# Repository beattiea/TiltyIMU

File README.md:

TiltyIMU
========

This repository contains all files relevant to the TiltyIMU family of circuit boards

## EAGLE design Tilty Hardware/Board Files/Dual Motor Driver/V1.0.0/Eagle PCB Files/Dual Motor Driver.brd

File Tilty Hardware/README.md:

Tilty Hardware
==============

Tilty board Eagle files, libraries, and part datasheets

Hardware revision naming scheme: Production Version . Major revision version . Minor revision version

Examples:  
V0.1.2 = Non-production, first major revision, second minor revision (would become V1.0.0 when it begins production)  
V1.0.0 = First production version, no major or minor revisions  
V1.1.0 = First majorly revised production version with no minor revisions (would become V2.0.0 when it begins production)

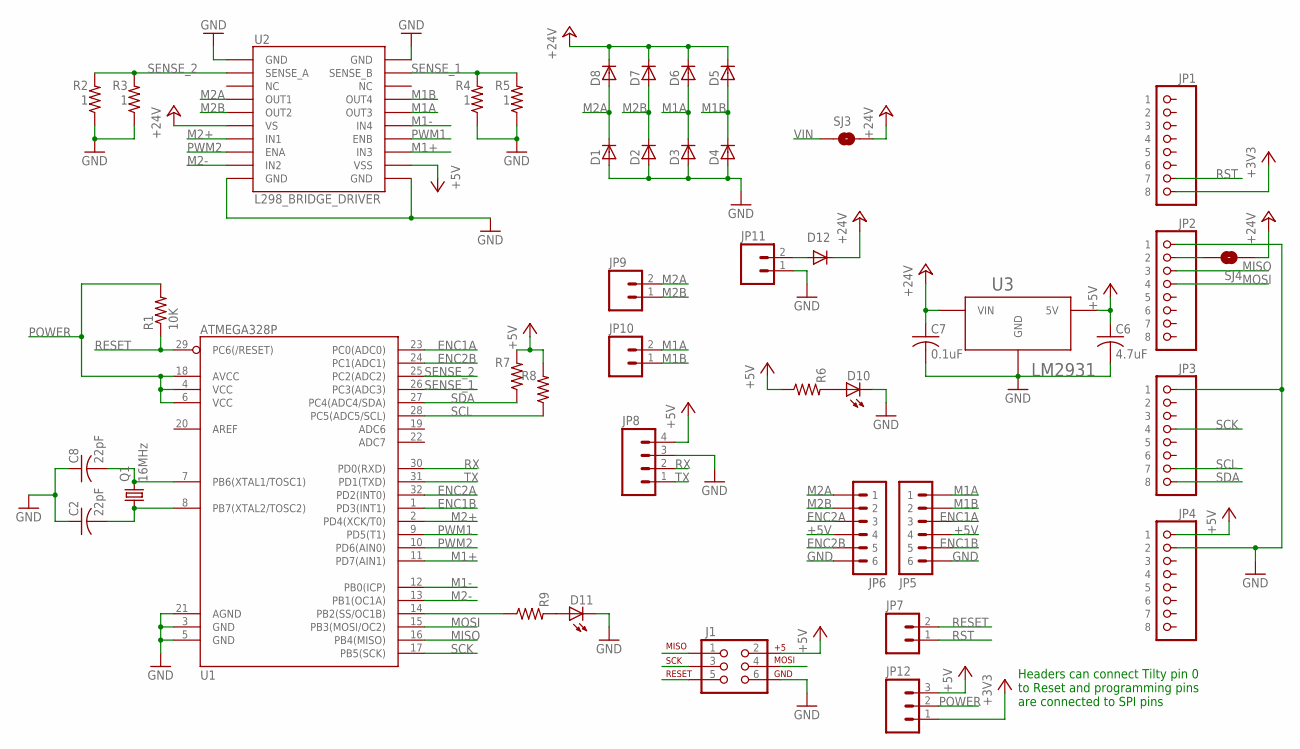
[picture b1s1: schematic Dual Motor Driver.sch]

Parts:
C2, C8: 22pF; C0603
C6: 4.7uF; C0603
C7: 0.1uF; C0603
D1, D2, D3, D4, D5, D6, D7, D8: D-SOD123; SOD123; PART# CDBW140-G
D10, D11: LED-GREENLED-0805_NO_SILK; LED-0805
D12: DIODESMB; SMB-DIODE
J1: AVR_SPI_PRG_62X3_LOCK; 2X3_LOCK
JP1, JP2, JP3, JP4: 8-PIN_HEADER; 8-PIN_RECEPTACLE_LOCK_NO-SS
JP5, JP6: 6PIN-SH_RIGHT_ANGLE; 6PIN-SH_SERIES_RA; PART# SM06B-SRSS-TB(LF)(SN)
JP7, JP9, JP10, JP11: M02PTH; 1X02
JP8: M04PTH; 1X04
JP12: M03PTH; 1X03
Q1: 16MHz; CTS406; PART# 406C35D16M00000
R1: 10K; R0603
R2, R3, R4, R5: 1; R0603
R6, R7, R8, R9: R-US_R0603; R0603
SJ3: SOLDERJUMPERNC; SJ_2S
SJ4: SOLDERJUMPERTRACE; SJ_2S-TRACE
U1: ATMEGA328P; TQFP32-08
U2: L298_BRIDGE_DRIVER; POWERSO20
U3: LM2931; TO263

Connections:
+3V3: JP1.P$8 (8), JP12.1
+5V: C6.1, J1.2, JP4.P$1 (1), JP5.P$4 (4), JP6.P$4 (4), JP8.4, JP12.3, R6.1, R7.2, R8.2, U2.12 (VSS), U3.P$3 (5V)
+24V: C7.1, D5.1 (C), D6.1 (C), D7.1 (C), D8.1 (C), D12.C, SJ3.2, SJ4.1, U2.6 (VS), U3.P$2 (VIN)
ENC1A: JP5.P$3 (3), U1.23 (PC0(ADC0))
ENC1B: JP5.P$5 (5), U1.1 (PD3(INT1))
ENC2A: JP6.P$3 (3), U1.32 (PD2(INT0))
ENC2B: JP6.P$5 (5), U1.24 (PC1(ADC1))
GND: C2.1, C6.2, C7.2, C8.1, D1.2 (A), D2.2 (A), D3.2 (A), D4.2 (A), D10.2 (C), D11.2 (C), J1.6, JP2.P$1 (1), JP3.P$1 (1), JP4.P$2 (2), JP5.P$6 (6), JP6.P$6 (6), JP8.3, JP11.1, R2.1, R3.1, R4.1, R5.1, U1.3 (GND), U1.5 (GND), U1.21 (AGND), U2.1 (GND), U2.10 (GND), U2.11 (GND), U2.20 (GND), U3.P$1 (GND)
M1+: U1.11 (PD7(AIN1)), U2.13 (IN3)
M1-: U1.12 (PB0(ICP)), U2.15 (IN4)
M1A: D3.1 (C), D6.2 (A), JP5.P$1 (1), JP10.2, U2.16 (OUT3)
M1B: D4.1 (C), D5.2 (A), JP5.P$2 (2), JP10.1, U2.17 (OUT4)
M2+: U1.2 (PD4(XCK/T0)), U2.7 (IN1)
M2-: U1.13 (PB1(OC1A)), U2.9 (IN2)
M2A: D1.1 (C), D8.2 (A), JP6.P$1 (1), JP9.2, U2.4 (OUT1)
M2B: D2.1 (C), D7.2 (A), JP6.P$2 (2), JP9.1, U2.5 (OUT2)
MISO: J1.1, JP2.P$3 (3), U1.16 (PB4(MISO))
MOSI: J1.4, JP2.P$4 (4), U1.15 (PB3(MOSI/OC2))
unnamed: D10.1 (A), R6.2
unnamed: D11.1 (A), R9.2
unnamed: R9.1, U1.14 (PB2(SS/OC1B))
unnamed: JP2.P$2 (2), SJ4.2
unnamed: C8.2, Q1.3 (2), U1.7 (PB6(XTAL1/TOSC1))
unnamed: C2.2, Q1.1, U1.8 (PB7(XTAL2/TOSC2))
POWER: JP12.2, R1.2, U1.4 (VCC), U1.6 (VCC), U1.18 (AVCC)
PWM1: U1.9 (PD5(T1)), U2.14 (ENB)
PWM2: U1.10 (PD6(AIN0)), U2.8 (ENA)
RESET: J1.5, JP7.2, R1.1, U1.29 (PC6(/RESET))
RST: JP1.P$7 (7), JP7.1
RX: JP8.2, U1.30 (PD0(RXD))
SCK: J1.3, JP3.P$4 (4), U1.17 (PB5(SCK))
SCL: JP3.P$7 (7), R8.1, U1.28 (PC5(ADC5/SCL))
SDA: JP3.P$8 (8), R7.1, U1.27 (PC4(ADC4/SDA))
SENSE_1: R4.2, R5.2, U1.26 (PC3(ADC3)), U2.19 (SENSE_B)
SENSE_2: R2.2, R3.2, U1.25 (PC2(ADC2)), U2.2 (SENSE_A)
TX: JP8.1, U1.31 (PD1(TXD))
VIN: D12.A, JP11.2, SJ3.1

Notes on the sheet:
Headers can connect Tilty pin 0 to Reset and programming pins are connected to SPI pins

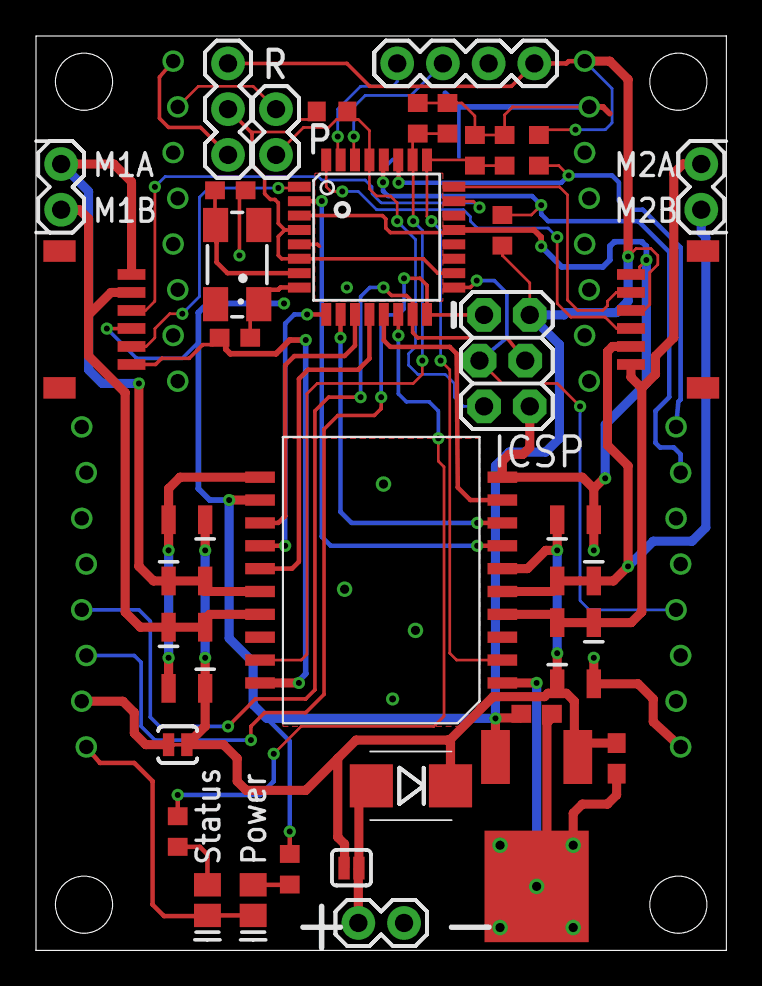
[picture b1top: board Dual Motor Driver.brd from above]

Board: 2 copper layers, 38.4 x 50.8 mm, 43 parts (0 on the bottom side), 37 nets.

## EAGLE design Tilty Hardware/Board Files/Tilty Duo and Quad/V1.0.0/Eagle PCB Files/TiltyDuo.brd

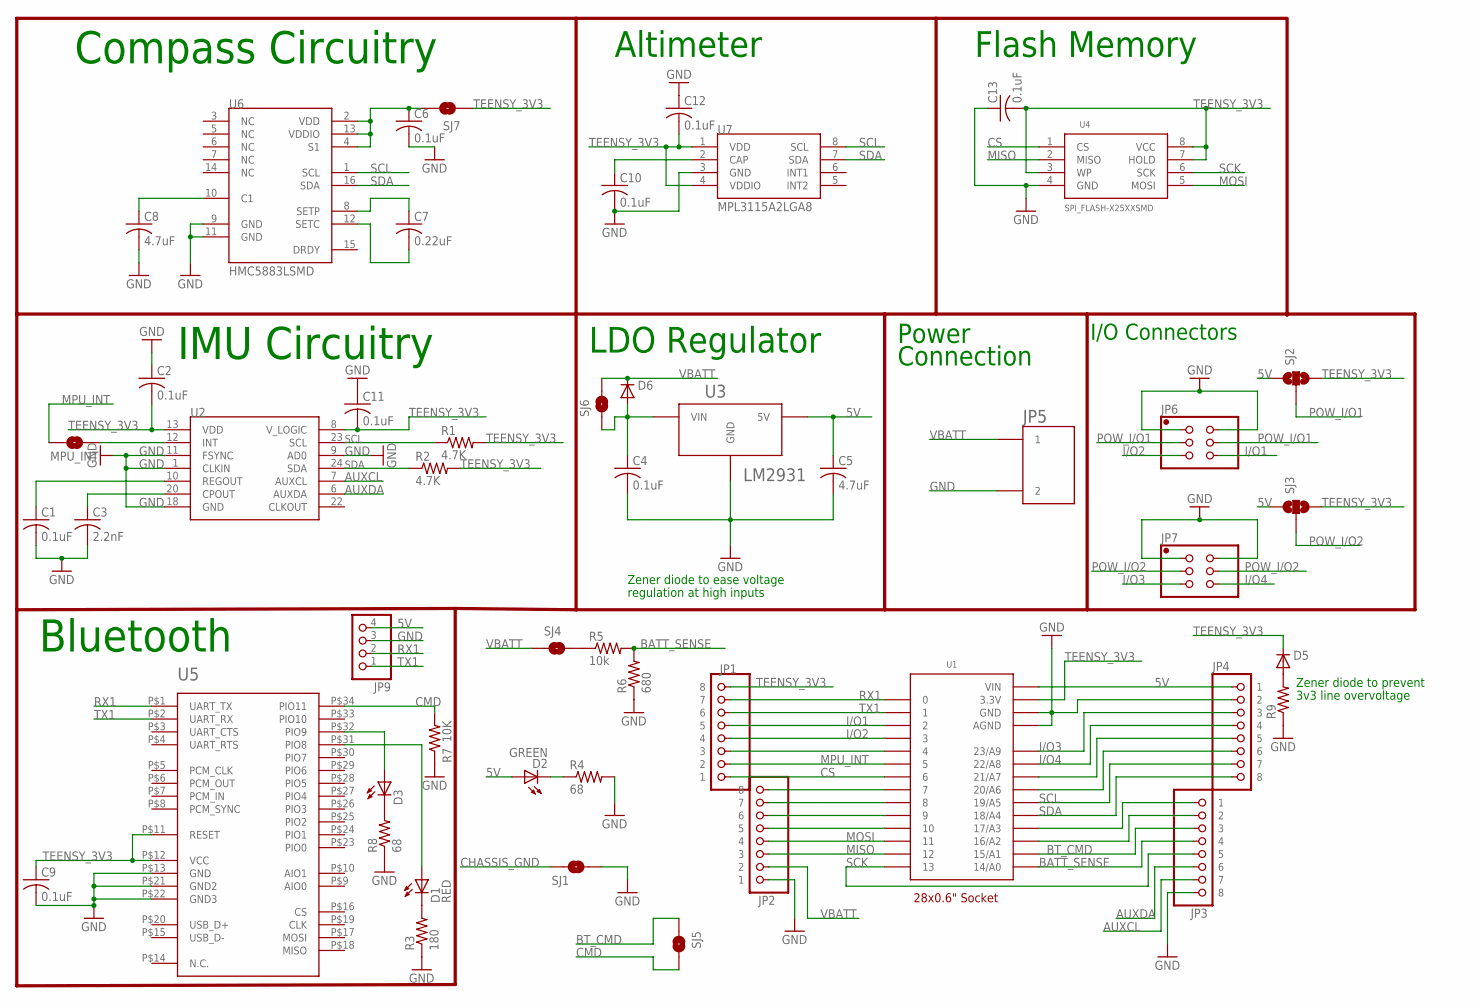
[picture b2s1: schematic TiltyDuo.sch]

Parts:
C1, C2, C4, C6, C9, C10, C11, C12, C13: 0.1uF; C0603
C3: 2.2nF; C0603
C5, C8: 4.7uF; C0603
C7: 0.22uF; C0603
D1: RED; LED-0805
D2: GREEN; LED-0805
D3: YELLOW; LED-0805
D5: DIODESOT23; SOT23-3; PART# BZX84C3V3LT1GOSCT-ND
D6: DIODE-DO214AA; DO214AA
JP1, JP2, JP3, JP4: 8-PIN_HEADER; 8-PIN_RECEPTACLE_LOCK_NO-SS
JP5: 2-POS_SMD_TERM_BLOCK; 2-POS_SMD_TERMINAL_BLOCK; PART# 277-2337-1-ND
JP6, JP7: PINHD-2X32X03_NO_SS_LOCK; 2X03_NO_SS_LOCK
JP9: PINHD-1X41X04_NO_SS_LOCKING; 1X04_NO_SS_LOCKING
MPU_INT: SOLDERJUMPERNO; SJ_2S-NO
R1, R2: 4.7K; R0603
R3: 180; R0603
R4, R8: 68; R0603
R5: 10k; R0603
R6: 680; R0603
R7: 10K; R0603
R9: R-US_R0603; R0603
SJ1: SOLDERJUMPERNO; SJ_2S-NO
SJ2: SOLDERJUMPER_2WAYPASTE1&2; SJ_3_PASTE1&2
SJ3: SOLDERJUMPER_2WAYS; SJ_3
SJ4, SJ5, SJ6, SJ7: SOLDERJUMPERTRACE; SJ_2S-TRACE
U1: TEENSY_3.0_OUTER-PINS28-DIP_SOCKET; 28-DIP; PART# AE10004-ND
U2: MPU-6050; QFN-24
U3: LM2931; TO263
U4: SPI_FLASH-X25XXSMD; SO08; PART# S25FL204K0TMFI043
U5: HC-09_BREAKOUT
U6: HMC5883LSMD; 16LPCC
U7: MPL3115A2LGA8; LGA8

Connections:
5V: C5.1, D2.1 (A), JP4.P$1 (1), JP9.4, SJ2.1, SJ3.1, U1.P$15 (VIN), U3.P$3 (5V)
AUXCL: JP3.P$7 (7), U2.7 (AUXCL)
AUXDA: JP3.P$6 (6), U2.6 (AUXDA)
BATT_SENSE: JP3.P$4 (4), R5.2, R6.2, U1.P$27 (14/A0)
BT_CMD: JP3.P$3 (3), SJ5.1, U1.P$26 (15/A1)
CHASSIS_GND: SJ1.1
CMD: R7.2, SJ5.2, U5.P$34 (PIO11)
CS: JP1.P$1 (1), U1.P$8 (6), U4.1 (CS)
GND: C1.2, C2.1, C3.2, C4.2, C5.2, C6.2, C8.2, C9.2, C10.2, C11.1, C12.1, C13.1, JP2.P$1 (1), JP3.P$8 (8), JP4.P$2 (2), JP5.P$4 (2), JP6.1, JP6.2, JP7.1, JP7.2, JP9.3, R3.1, R4.2, R6.1, R7.1, R8.1, R9.1, SJ1.2, U1.P$1 (GND), U1.P$16 (AGND), U2.1 (CLKIN), U2.9 (AD0), U2.11 (FSYNC), U2.18 (GND), U3.P$1 (GND), U4.4 (GND), U5.P$13 (GND), U5.P$21 (GND2), U5.P$22 (GND3), U6.9 (GND), U6.11 (GND), U7.3 (GND)
I/O1: JP1.P$5 (5), JP6.6, U1.P$4 (2)
I/O2: JP1.P$4 (4), JP6.5, U1.P$5 (3)
I/O3: JP4.P$3 (3), JP7.5, U1.P$18 (23/A9)
I/O4: JP4.P$4 (4), JP7.6, U1.P$19 (22/A8)
MISO: JP2.P$3 (3), U1.P$14 (12), U4.2 (MISO)
MOSI: JP2.P$4 (4), U1.P$13 (11), U4.5 (MOSI)
MPU_INT: JP1.P$2 (2), MPU_INT.1, U1.P$7 (5)
unnamed: C1.1, U2.10 (REGOUT)
unnamed: C3.1, U2.20 (CPOUT)
unnamed: D1.2 (C), R3.2
unnamed: C7.1, U6.8 (SETP)
unnamed: C7.2, U6.12 (SETC)
unnamed: JP1.P$3 (3), U1.P$6 (4)
unnamed: JP2.P$5 (5), U1.P$12 (10)
unnamed: R5.1, SJ4.2
unnamed: JP3.P$1 (1), U1.P$24 (17/A3)
unnamed: C8.1, U6.10 (C1)
unnamed: JP2.P$6 (6), U1.P$11 (9)
unnamed: D2.2 (C), R4.1
unnamed: D1.1 (A), U5.P$31 (PIO8)
unnamed: MPU_INT.2, U2.12 (INT)
unnamed: C6.1, SJ7.2, U6.2 (VDD), U6.4 (S1), U6.13 (VDDIO)
unnamed: JP4.P$5 (5), U1.P$20 (21/A7)
unnamed: JP4.P$6 (6), U1.P$21 (20/A6)
unnamed: C10.1, U7.2 (CAP)
unnamed: D5.1 (A), R9.2
unnamed: JP3.P$2 (2), U1.P$25 (16/A2)
unnamed: D3.2 (C), R8.2
POW_I/O1: JP6.3, JP6.4, SJ2.2
POW_I/O2: JP7.3, JP7.4, SJ3.2
RX1: JP1.P$7 (7), JP9.2, U1.P$2 (0), U5.P$1 (UART_TX)
RX3: JP2.P$8 (8), U1.P$9 (7)
SCK: JP3.P$5 (5), U1.P$28 (13), U4.6 (SCK)
SCL: JP4.P$7 (7), R1.1, U1.P$22 (19/A5), U2.23 (SCL), U6.1 (SCL), U7.8 (SCL)
SDA: JP4.P$8 (8), R2.1, U1.P$23 (18/A4), U2.24 (SDA), U6.16 (SDA), U7.7 (SDA)
TEENSY_3V3: C2.2, C9.1, C11.2, C12.2, C13.2, D5.3 (C), JP1.P$8 (8), R1.2, R2.2, SJ2.3, SJ3.3, SJ7.1, U1.P$17 (3.3V), U2.8 (V_LOGIC), U2.13 (VDD), U4.3 (WP), U4.7 (HOLD), U4.8 (VCC), U5.P$11 (RESET), U5.P$12 (VCC), U7.1 (VDD), U7.4 (VDDIO)
TX1: JP1.P$6 (6), JP9.1, U1.P$3 (1), U5.P$2 (UART_RX)
TX3: JP2.P$7 (7), U1.P$10 (8)
VBATT: C4.1, D6.A, D6.C, JP2.P$2 (2), JP5.P$3 (1), SJ4.1, SJ6.1, SJ6.2, U3.P$2 (VIN)
YEL_LED: D3.1 (A), U5.P$32 (PIO9)

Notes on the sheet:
IMU Circuitry
28x0.6" Socket
LDO Regulator
Bluetooth
Power
Connection
I/O Connectors
Compass Circuitry
Altimeter
Flash Memory
Zener diode to prevent
3v3 line overvoltage
Zener diode to ease voltage
regulation at high inputs

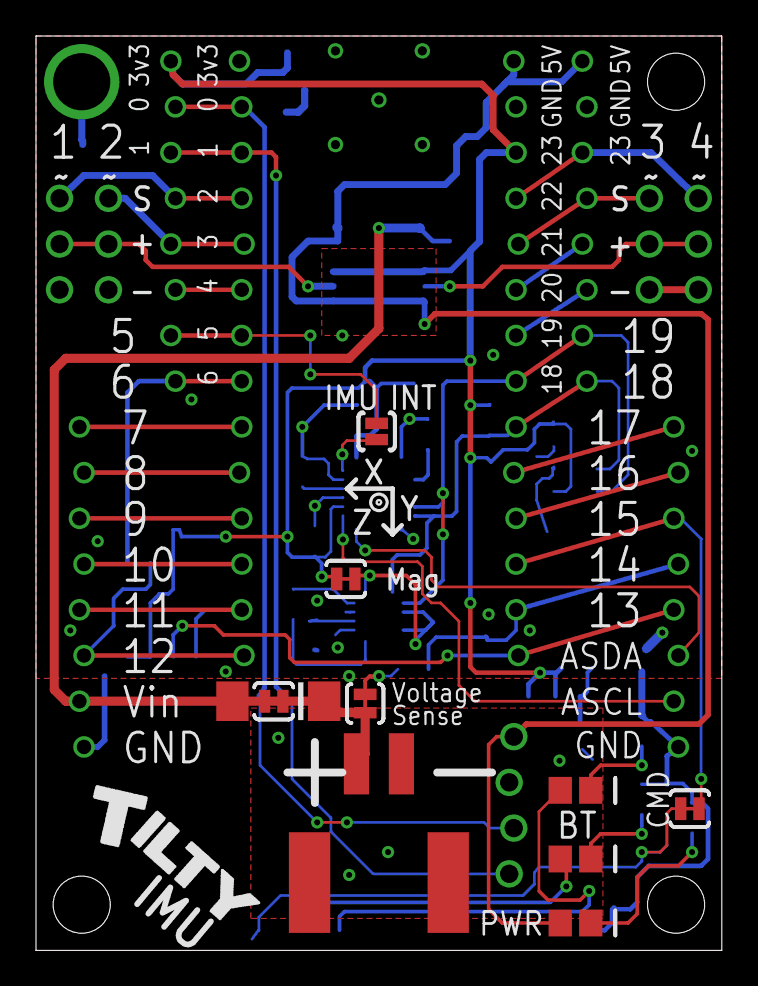
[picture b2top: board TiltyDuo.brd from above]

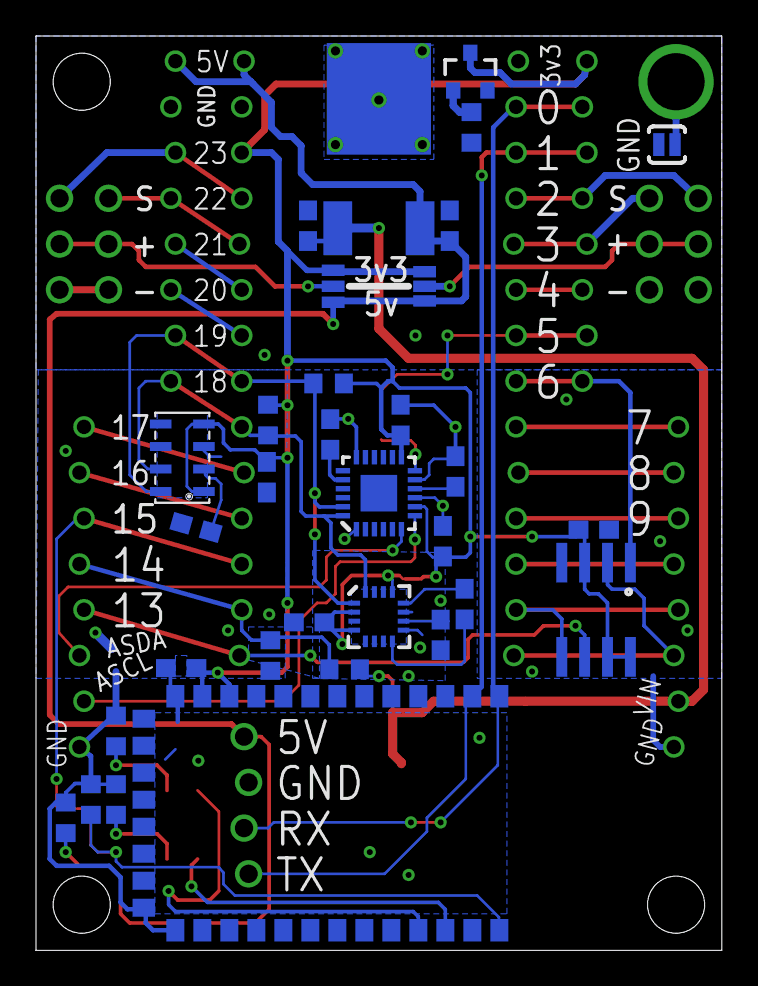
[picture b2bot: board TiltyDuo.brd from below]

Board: 2 copper layers, 38.1 x 50.8 mm, 50 parts (32 on the bottom side), 48 nets.

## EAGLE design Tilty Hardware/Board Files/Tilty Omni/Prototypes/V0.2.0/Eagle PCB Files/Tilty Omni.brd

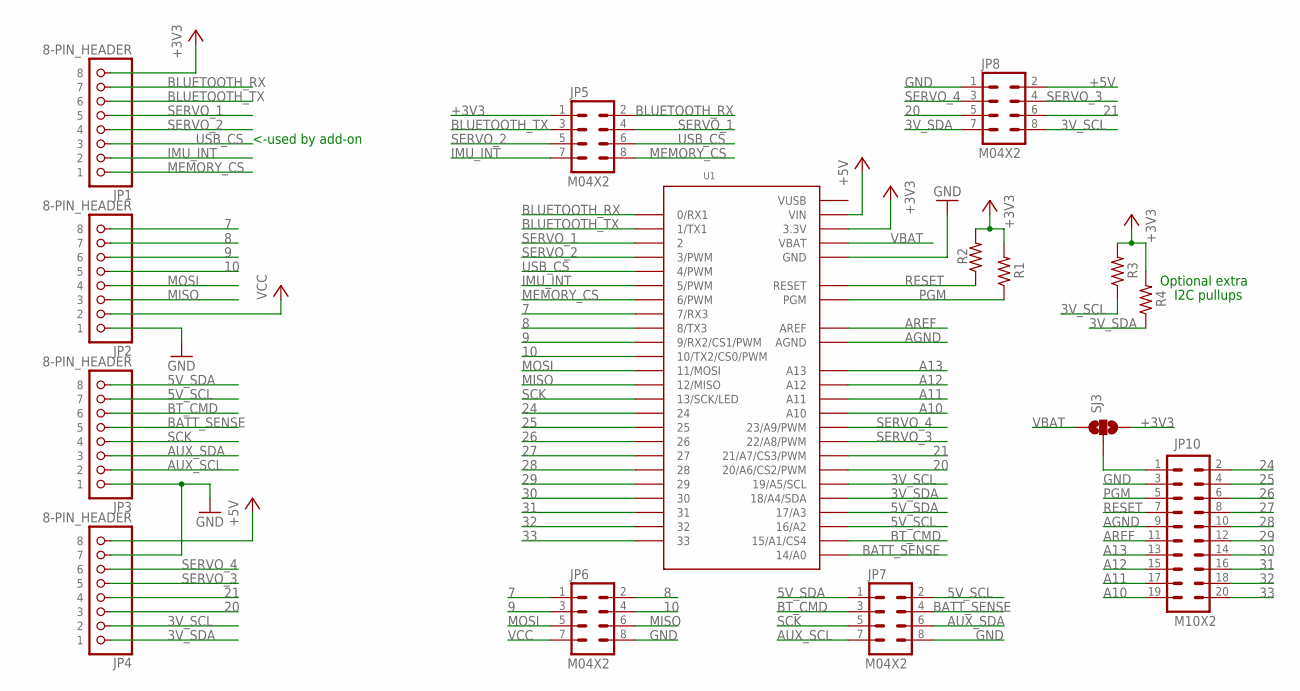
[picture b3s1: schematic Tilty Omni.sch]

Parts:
JP1, JP2, JP3, JP4: 8-PIN_HEADER; 8-PIN_RECEPTACLE_LOCK_NO-SS
JP5, JP6, JP7, JP8: M04X2; 2X4
JP10: M10X2; 2X10
R1, R2, R3, R4: 10k; R0603
SJ3: SOLDERJUMPER_2WAYPASTE2&3; SJ_3_PASTE2&3
U1: TEENSY_3.0_ALLPINS

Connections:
3V_SCL: JP4.P$2 (2), JP8.8, R3.1, U1.19/A5 (19/A5/SCL)
3V_SDA: JP4.P$1 (1), JP8.7, R4.1, U1.18/A4 (18/A4/SDA)
5V_SCL: JP3.P$7 (7), JP7.2, U1.16/A2
5V_SDA: JP3.P$8 (8), JP7.1, U1.17/A3
7: JP2.P$8 (8), JP6.1, U1.7 (7/RX3)
8: JP2.P$7 (7), JP6.2, U1.8 (8/TX3)
9: JP2.P$6 (6), JP6.3, U1.9 (9/RX2/CS1/PWM)
10: JP2.P$5 (5), JP6.4, U1.10 (10/TX2/CS0/PWM)
20: JP4.P$3 (3), JP8.5, U1.20/A6 (20/A6/CS2/PWM)
21: JP4.P$4 (4), JP8.6, U1.21/A7 (21/A7/CS3/PWM)
24: JP10.2, U1.24
25: JP10.4, U1.25
26: JP10.6, U1.26
27: JP10.8, U1.27
28: JP10.10, U1.28
29: JP10.12, U1.29
30: JP10.14, U1.30
31: JP10.16, U1.31
32: JP10.18, U1.32
33: JP10.20, U1.33
+3V3: JP1.P$8 (8), JP5.1, R1.2, R2.2, R3.2, R4.2, SJ3.3, U1.3.3V, U1.3.3V1 (3.3V), U1.3.3V2 (3.3V)
+5V: JP4.P$8 (8), JP8.2, U1.VIN
A10: JP10.19, U1.A10
A11: JP10.17, U1.A11
A12: JP10.15, U1.A12
A13: JP10.13, U1.A13
AGND: JP10.9, U1.AGND
AREF: JP10.11, U1.AREF
AUX_SCL: JP3.P$2 (2), JP7.7
AUX_SDA: JP3.P$3 (3), JP7.6
BATT_SENSE: JP3.P$5 (5), JP7.4, U1.14/A0
BLUETOOTH_RX: JP1.P$7 (7), JP5.2, U1.0 (0/RX1)
BLUETOOTH_TX: JP1.P$6 (6), JP5.3, U1.1 (1/TX1)
BT_CMD: JP3.P$6 (6), JP7.3, U1.15/A1 (15/A1/CS4)
GND: JP2.P$1 (1), JP3.P$1 (1), JP4.P$7 (7), JP6.8, JP7.8, JP8.1, JP10.3, U1.GND, U1.GND1 (GND), U1.GND2 (GND)
IMU_INT: JP1.P$2 (2), JP5.7, U1.5 (5/PWM)
MEMORY_CS: JP1.P$1 (1), JP5.8, U1.6 (6/PWM)
MISO: JP2.P$3 (3), JP6.6, U1.12 (12/MISO)
MOSI: JP2.P$4 (4), JP6.5, U1.11 (11/MOSI)
unnamed: JP10.1, SJ3.2
PGM: JP10.5, R1.1, U1.PGM
RESET: JP10.7, R2.1, U1.RESET
SCK: JP3.P$4 (4), JP7.5, U1.13 (13/SCK/LED)
SERVO_1: JP1.P$5 (5), JP5.4, U1.2
SERVO_2: JP1.P$4 (4), JP5.5, U1.3 (3/PWM)
SERVO_3: JP4.P$5 (5), JP8.4, U1.22/A8 (22/A8/PWM)
SERVO_4: JP4.P$6 (6), JP8.3, U1.23/A9 (23/A9/PWM)
USB_CS: JP1.P$3 (3), JP5.6, U1.4 (4/PWM)
VBAT: SJ3.1, U1.VBAT
VCC: JP2.P$2 (2), JP6.7
VUSB: U1.VUSB

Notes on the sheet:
<-used by add-on
Optional extra
I2C pullups

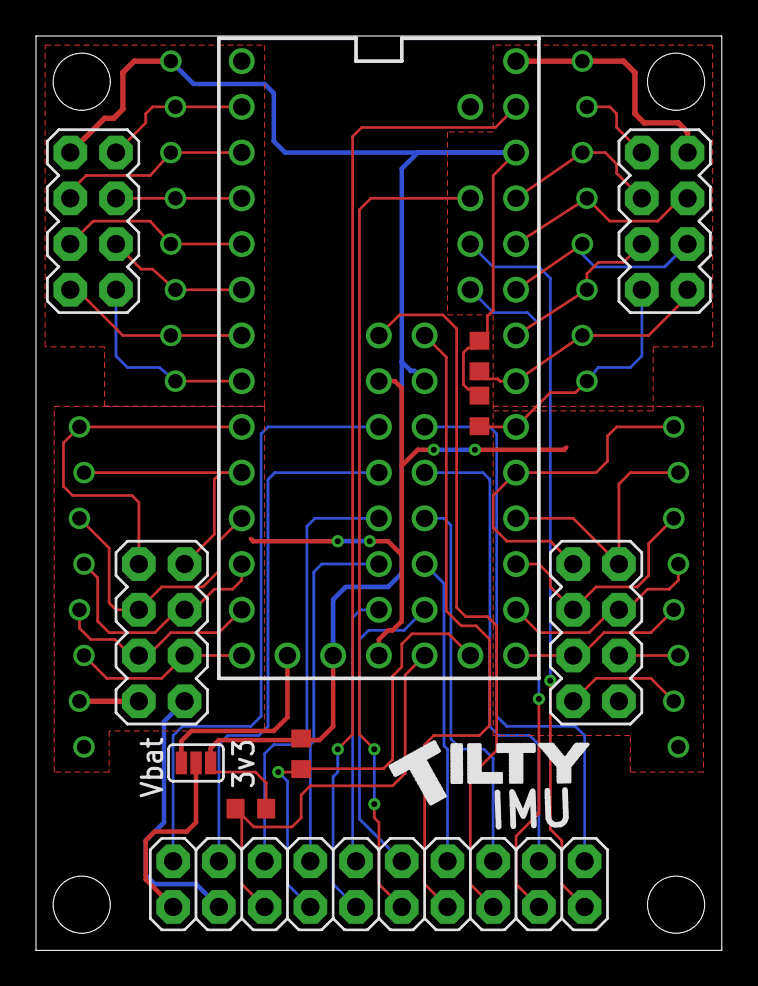
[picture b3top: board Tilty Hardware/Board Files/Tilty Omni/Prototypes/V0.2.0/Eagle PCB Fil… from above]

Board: 2 copper layers, 38.1 x 50.8 mm, 15 parts (0 on the bottom side), 50 nets.

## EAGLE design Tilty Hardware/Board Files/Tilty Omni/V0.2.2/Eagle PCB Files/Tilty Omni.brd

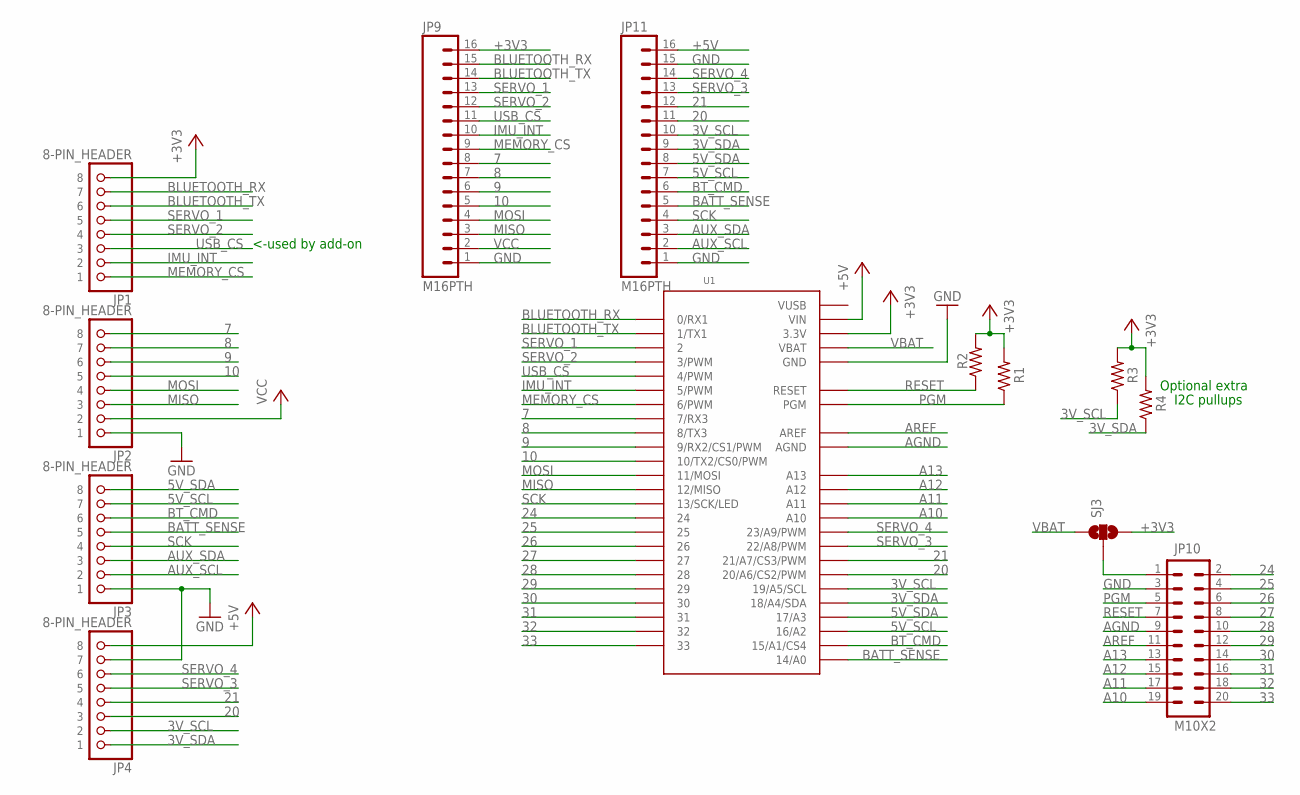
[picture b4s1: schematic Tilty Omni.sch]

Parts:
JP1, JP2, JP3, JP4: 8-PIN_HEADER; 8-PIN_RECEPTACLE_LOCK_NO-SS
JP9, JP11: M16PTH; 1X16
JP10: M10X2; 2X10
R1, R2, R3, R4: 10k; R0603
SJ3: SOLDERJUMPER_2WAYPASTE2&3; SJ_3_PASTE2&3
U1: TEENSY_3.0_ALLPINS

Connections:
3V_SCL: JP4.P$2 (2), JP11.10, R3.1, U1.19/A5 (19/A5/SCL)
3V_SDA: JP4.P$1 (1), JP11.9, R4.1, U1.18/A4 (18/A4/SDA)
5V_SCL: JP3.P$7 (7), JP11.7, U1.16/A2
5V_SDA: JP3.P$8 (8), JP11.8, U1.17/A3
7: JP2.P$8 (8), JP9.8, U1.7 (7/RX3)
8: JP2.P$7 (7), JP9.7, U1.8 (8/TX3)
9: JP2.P$6 (6), JP9.6, U1.9 (9/RX2/CS1/PWM)
10: JP2.P$5 (5), JP9.5, U1.10 (10/TX2/CS0/PWM)
20: JP4.P$3 (3), JP11.11, U1.20/A6 (20/A6/CS2/PWM)
21: JP4.P$4 (4), JP11.12, U1.21/A7 (21/A7/CS3/PWM)
24: JP10.2, U1.24
25: JP10.4, U1.25
26: JP10.6, U1.26
27: JP10.8, U1.27
28: JP10.10, U1.28
29: JP10.12, U1.29
30: JP10.14, U1.30
31: JP10.16, U1.31
32: JP10.18, U1.32
33: JP10.20, U1.33
+3V3: JP1.P$8 (8), JP9.16, R1.2, R2.2, R3.2, R4.2, SJ3.3, U1.3.3V, U1.3.3V1 (3.3V), U1.3.3V2 (3.3V)
+5V: JP4.P$8 (8), JP11.16, U1.VIN
A10: JP10.19, U1.A10
A11: JP10.17, U1.A11
A12: JP10.15, U1.A12
A13: JP10.13, U1.A13
AGND: JP10.9, U1.AGND
AREF: JP10.11, U1.AREF
AUX_SCL: JP3.P$2 (2), JP11.2
AUX_SDA: JP3.P$3 (3), JP11.3
BATT_SENSE: JP3.P$5 (5), JP11.5, U1.14/A0
BLUETOOTH_RX: JP1.P$7 (7), JP9.15, U1.0 (0/RX1)
BLUETOOTH_TX: JP1.P$6 (6), JP9.14, U1.1 (1/TX1)
BT_CMD: JP3.P$6 (6), JP11.6, U1.15/A1 (15/A1/CS4)
GND: JP2.P$1 (1), JP3.P$1 (1), JP4.P$7 (7), JP9.1, JP10.3, JP11.1, JP11.15, U1.GND, U1.GND1 (GND), U1.GND2 (GND)
IMU_INT: JP1.P$2 (2), JP9.10, U1.5 (5/PWM)
MEMORY_CS: JP1.P$1 (1), JP9.9, U1.6 (6/PWM)
MISO: JP2.P$3 (3), JP9.3, U1.12 (12/MISO)
MOSI: JP2.P$4 (4), JP9.4, U1.11 (11/MOSI)
unnamed: JP10.1, SJ3.2
PGM: JP10.5, R1.1, U1.PGM
RESET: JP10.7, R2.1, U1.RESET
SCK: JP3.P$4 (4), JP11.4, U1.13 (13/SCK/LED)
SERVO_1: JP1.P$5 (5), JP9.13, U1.2
SERVO_2: JP1.P$4 (4), JP9.12, U1.3 (3/PWM)
SERVO_3: JP4.P$5 (5), JP11.13, U1.22/A8 (22/A8/PWM)
SERVO_4: JP4.P$6 (6), JP11.14, U1.23/A9 (23/A9/PWM)
USB_CS: JP1.P$3 (3), JP9.11, U1.4 (4/PWM)
VBAT: SJ3.1, U1.VBAT
VCC: JP2.P$2 (2), JP9.2
VUSB: U1.VUSB

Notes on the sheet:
<-used by add-on
Optional extra
I2C pullups

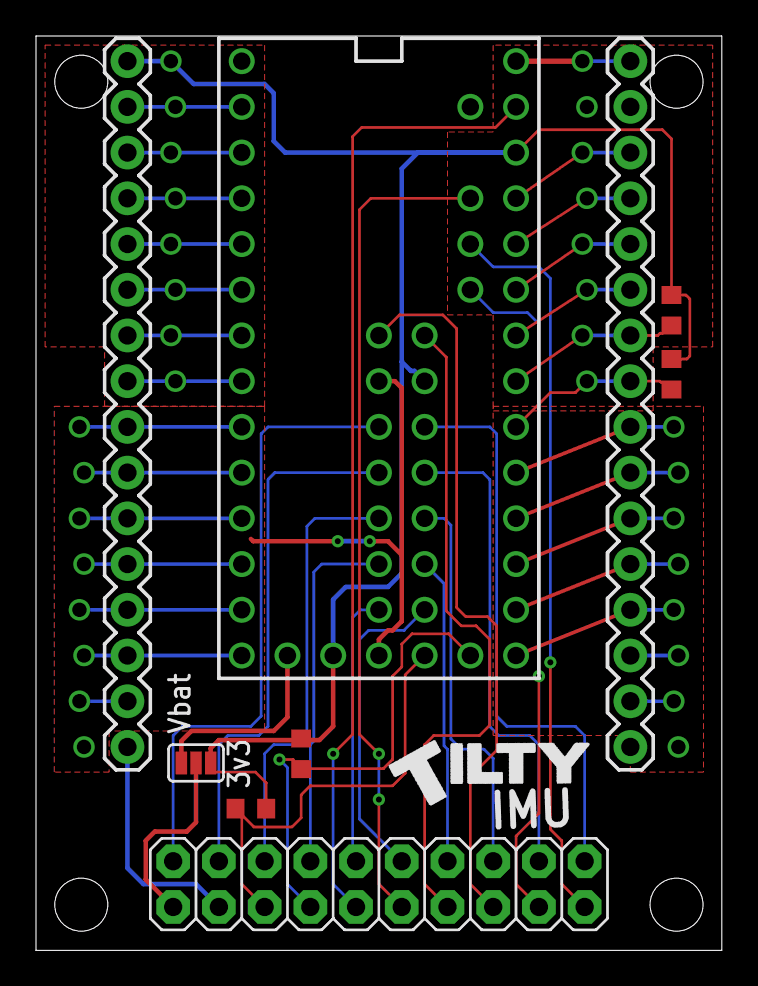
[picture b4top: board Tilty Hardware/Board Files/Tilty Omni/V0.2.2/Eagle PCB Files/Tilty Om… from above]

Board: 2 copper layers, 38.1 x 50.8 mm, 13 parts (0 on the bottom side), 50 nets.

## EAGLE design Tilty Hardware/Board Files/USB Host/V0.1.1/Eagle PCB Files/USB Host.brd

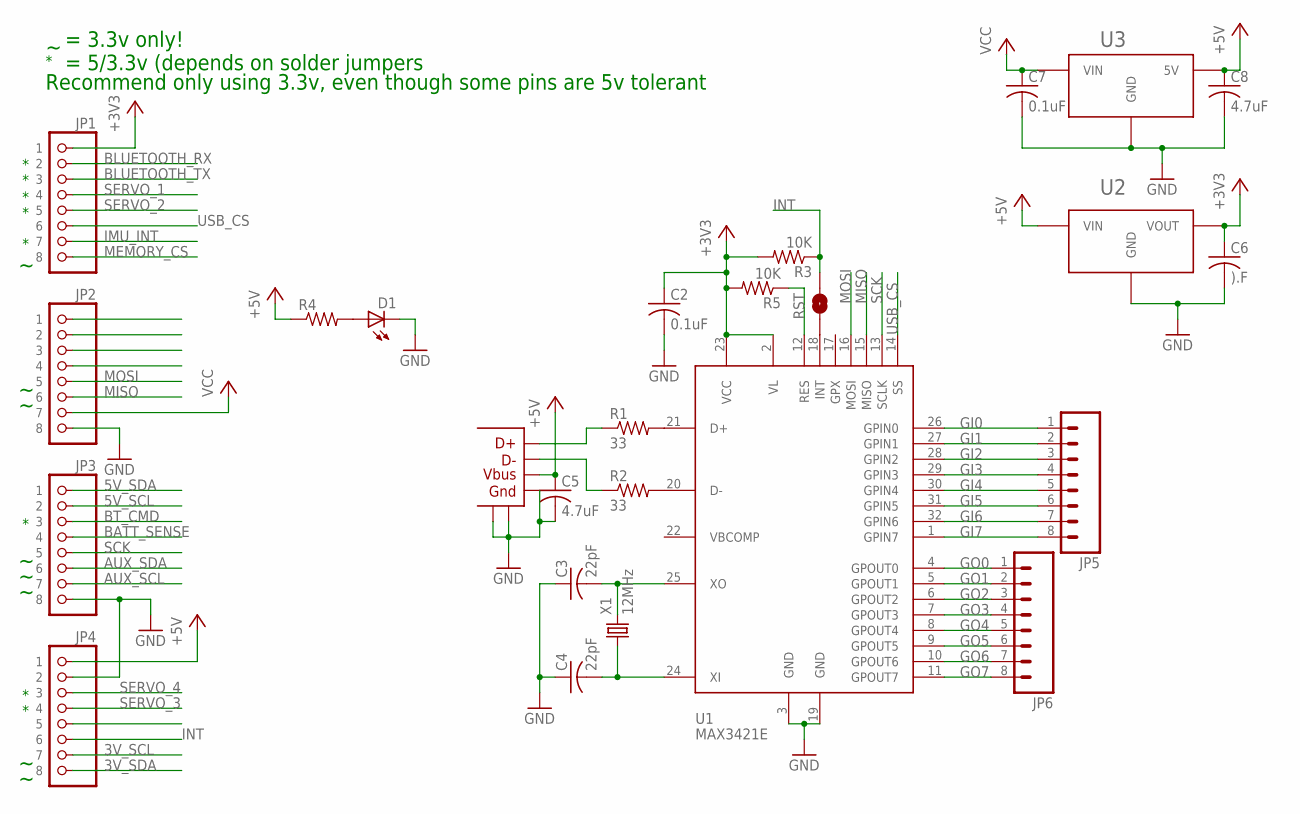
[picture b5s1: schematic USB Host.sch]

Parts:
C2, C7: 0.1uF; C0603
C3, C4: 22pF; C0603
C5, C8: 4.7uF; C0603
C6: ).F; C0603
D1: LED-GREENLED-0805_NO_SILK; LED-0805
JP1, JP2, JP3, JP4: 8-PIN_HEADER; 8-PIN_RECEPTACLE_LOCK_NO-SS
JP5, JP6: M081X08; 1X08
R1, R2: 33; R0603
R3, R5: 10K; R0603
R4: R-US_R0603; R0603
SJ1: SOLDERJUMPERTRACE; SJ_2S-TRACE
U1: MAX3421E; TQFP32_8MIL
U2: AP7313SOT23R; SOT23
U3: LM2931; TO263
U$1: USB_SOCKETTYPE-A; USB_SOCKET; PART# USB-A1HSW6
X1: 12MHz; CRYSTAL-TXC-7A; PART# 7A-12.000MAAE-T

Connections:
3V_SCL: JP4.P$7 (7)
3V_SDA: JP4.P$8 (8)
5V_SCL: JP3.P$2 (2)
5V_SDA: JP3.P$1 (1)
+3V3: C2.1, C6.1, JP1.P$1 (1), R3.2, R5.2, U1.2 (VL), U1.23 (VCC), U2.P$2 (VOUT)
+5V: C5.1, C8.1, JP4.P$1 (1), R4.1, U2.P$3 (VIN), U3.P$3 (5V), U$1.P$1 (VBUS)
AUX_SCL: JP3.P$7 (7)
AUX_SDA: JP3.P$6 (6)
BATT_SENSE: JP3.P$4 (4)
BLUETOOTH_RX: JP1.P$2 (2)
BLUETOOTH_TX: JP1.P$3 (3)
BT_CMD: JP3.P$3 (3)
GI0: JP5.1, U1.26 (GPIN0)
GI1: JP5.2, U1.27 (GPIN1)
GI2: JP5.3, U1.28 (GPIN2)
GI3: JP5.4, U1.29 (GPIN3)
GI4: JP5.5, U1.30 (GPIN4)
GI5: JP5.6, U1.31 (GPIN5)
GI6: JP5.7, U1.32 (GPIN6)
GI7: JP5.8, U1.1 (GPIN7)
GND: C2.2, C3.1, C4.1, C5.2, C6.2, C7.2, C8.2, D1.2 (C), JP2.P$8 (8), JP3.P$8 (8), JP4.P$2 (2), U1.3 (GND), U1.19 (GND), U2.P$1 (GND), U3.P$1 (GND), U$1.P$4 (GND), U$1.P$5, U$1.P$6
GO0: JP6.1, U1.4 (GPOUT0)
GO1: JP6.2, U1.5 (GPOUT1)
GO2: JP6.3, U1.6 (GPOUT2)
GO3: JP6.4, U1.7 (GPOUT3)
GO4: JP6.5, U1.8 (GPOUT4)
GO5: JP6.6, U1.9 (GPOUT5)
GO6: JP6.7, U1.10 (GPOUT6)
GO7: JP6.8, U1.11 (GPOUT7)
IMU_INT: JP1.P$7 (7)
INT: JP4.P$6 (6), R3.1, SJ1.2
MEMORY_CS: JP1.P$8 (8)
MISO: JP2.P$6 (6), U1.15 (MISO)
MOSI: JP2.P$5 (5), U1.16 (MOSI)
unnamed: R2.2, U1.20 (D-)
unnamed: R1.2, U1.21 (D+)
unnamed: R2.1, U$1.P$2 (D-)
unnamed: R1.1, U$1.P$3 (D+)
unnamed: D1.1 (A), R4.2
unnamed: SJ1.1, U1.18 (INT)
unnamed: C4.2, U1.24 (XI), X1.P$1 (1)
unnamed: C3.2, U1.25 (XO), X1.P$2 (2)
RST: R5.1, U1.12 (RES)
SCK: JP3.P$5 (5), U1.13 (SCLK)
SERVO_1: JP1.P$4 (4)
SERVO_2: JP1.P$5 (5)
SERVO_3: JP4.P$4 (4)
SERVO_4: JP4.P$3 (3)
USB_CS: JP1.P$6 (6), U1.14 (SS)
VCC: C7.1, JP2.P$7 (7), U3.P$2 (VIN)

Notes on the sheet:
= 3.3v only!
= 5/3.3v (depends on solder jumpers
Recommend only using 3.3v, even though some pins are 5v tolerant

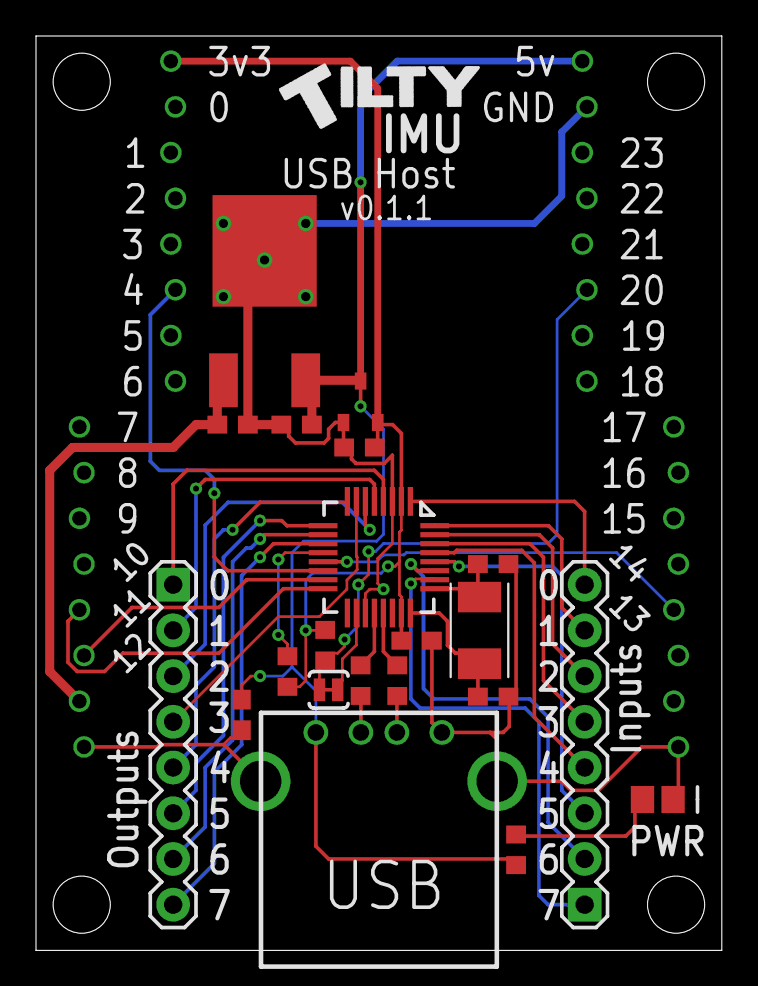
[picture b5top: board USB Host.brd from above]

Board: 2 copper layers, 38.1 x 50.8 mm, 25 parts (0 on the bottom side), 34 nets.

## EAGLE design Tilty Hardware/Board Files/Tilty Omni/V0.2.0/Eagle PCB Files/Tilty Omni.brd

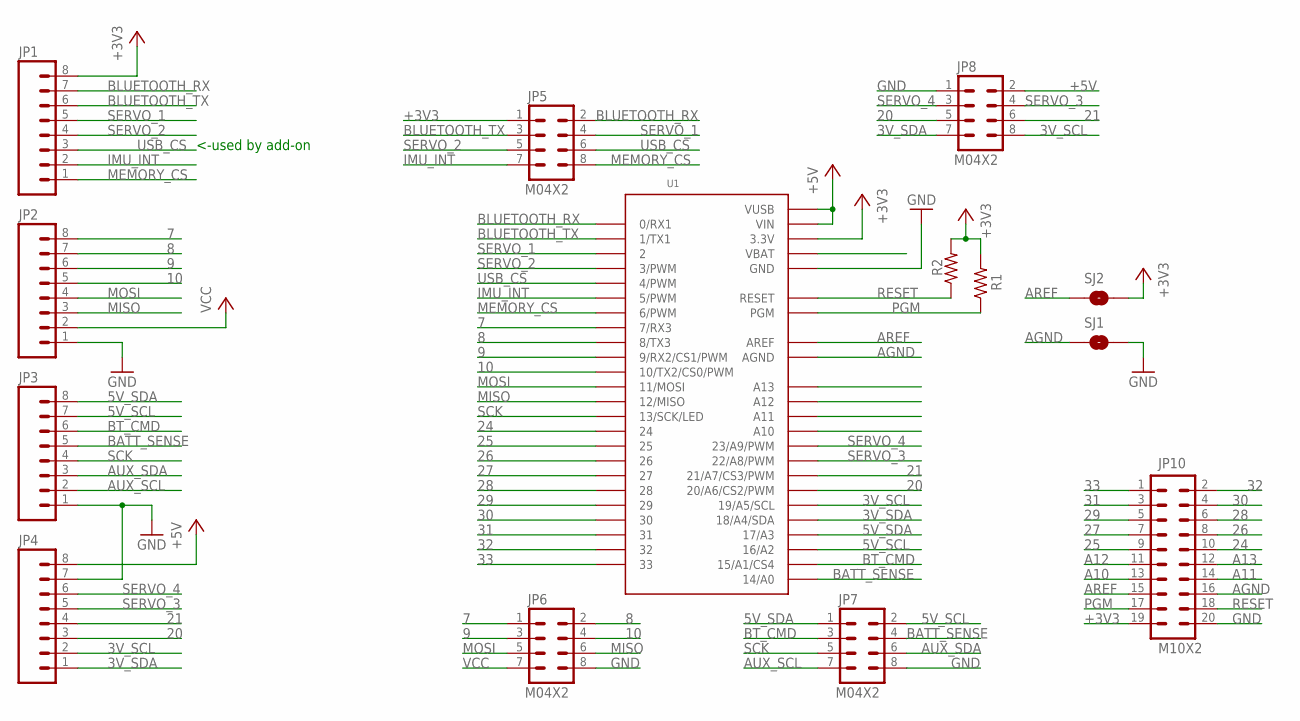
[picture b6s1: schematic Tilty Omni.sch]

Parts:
JP1, JP2, JP3, JP4: M081X08; 1X08
JP5, JP6, JP7, JP8: M04X2; 2X4
JP10: M10X2; 2X10
R1, R2: 10k; R0603
SJ1, SJ2: SOLDERJUMPERTRACE; SJ_2S-TRACE
U1: TEENSY_3.0_ALLPINS

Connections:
3V_SCL: JP4.2, JP8.8, U1.19/A5 (19/A5/SCL)
3V_SDA: JP4.1, JP8.7, U1.18/A4 (18/A4/SDA)
5V_SCL: JP3.7, JP7.2, U1.16/A2
5V_SDA: JP3.8, JP7.1, U1.17/A3
7: JP2.8, JP6.1, U1.7 (7/RX3)
8: JP2.7, JP6.2, U1.8 (8/TX3)
9: JP2.6, JP6.3, U1.9 (9/RX2/CS1/PWM)
10: JP2.5, JP6.4, U1.10 (10/TX2/CS0/PWM)
20: JP4.3, JP8.5, U1.20/A6 (20/A6/CS2/PWM)
21: JP4.4, JP8.6, U1.21/A7 (21/A7/CS3/PWM)
24: JP10.10, U1.24
25: JP10.9, U1.25
26: JP10.8, U1.26
27: JP10.7, U1.27
28: JP10.6, U1.28
29: JP10.5, U1.29
30: JP10.4, U1.30
31: JP10.3, U1.31
32: JP10.2, U1.32
33: JP10.1, U1.33
+3V3: JP1.8, JP5.1, JP10.19, R1.2, R2.2, SJ2.2, U1.3.3V, U1.3.3V1 (3.3V), U1.3.3V2 (3.3V)
+5V: JP4.8, JP8.2, U1.VIN, U1.VUSB
A10: JP10.13
A11: JP10.14
A12: JP10.11
A13: JP10.12, U1.A13
AGND: JP10.16, SJ1.1, U1.AGND
AREF: JP10.15, SJ2.1, U1.AREF
AUX_SCL: JP3.2, JP7.7
AUX_SDA: JP3.3, JP7.6
BATT_SENSE: JP3.5, JP7.4, U1.14/A0
BLUETOOTH_RX: JP1.7, JP5.2, U1.0 (0/RX1)
BLUETOOTH_TX: JP1.6, JP5.3, U1.1 (1/TX1)
BT_CMD: JP3.6, JP7.3, U1.15/A1 (15/A1/CS4)
GND: JP2.1, JP3.1, JP4.7, JP6.8, JP7.8, JP8.1, JP10.20, SJ1.2, U1.GND, U1.GND1 (GND), U1.GND2 (GND)
IMU_INT: JP1.2, JP5.7, U1.5 (5/PWM)
MEMORY_CS: JP1.1, JP5.8, U1.6 (6/PWM)
MISO: JP2.3, JP6.6, U1.12 (12/MISO)
MOSI: JP2.4, JP6.5, U1.11 (11/MOSI)
PGM: JP10.17, R1.1, U1.PGM
RESET: JP10.18, R2.1, U1.RESET
SCK: JP3.4, JP7.5, U1.13 (13/SCK/LED)
SERVO_1: JP1.5, JP5.4, U1.2
SERVO_2: JP1.4, JP5.5, U1.3 (3/PWM)
SERVO_3: JP4.5, JP8.4, U1.22/A8 (22/A8/PWM)
SERVO_4: JP4.6, JP8.3, U1.23/A9 (23/A9/PWM)
USB_CS: JP1.3, JP5.6, U1.4 (4/PWM)
VCC: JP2.2, JP6.7

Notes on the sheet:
<-used by add-on

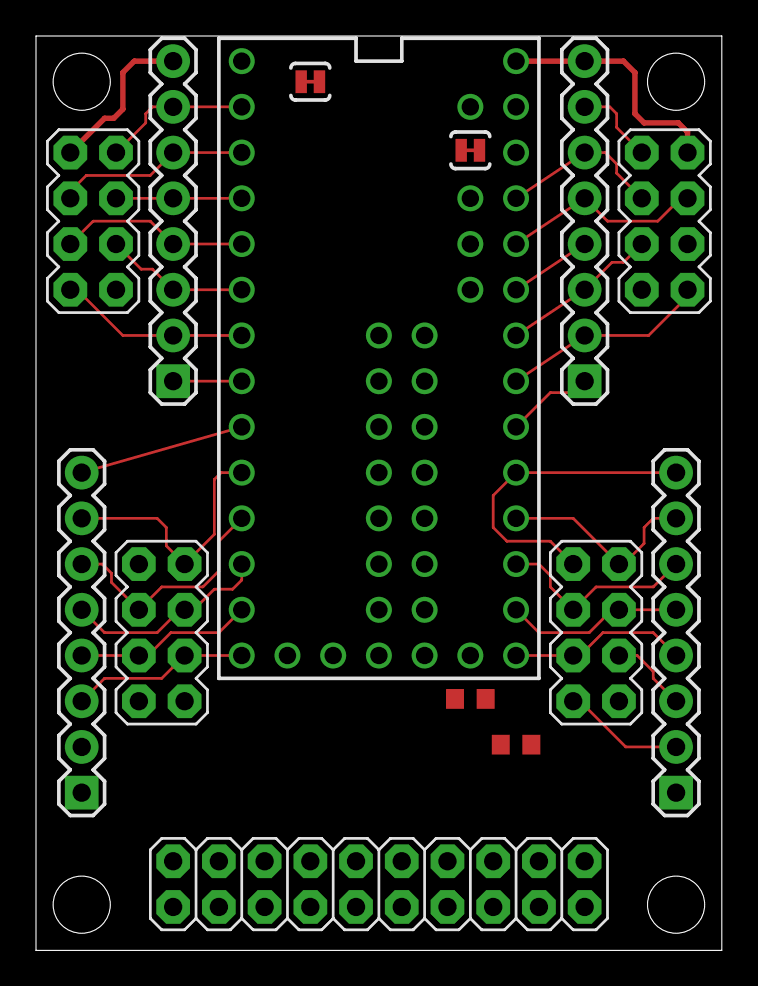
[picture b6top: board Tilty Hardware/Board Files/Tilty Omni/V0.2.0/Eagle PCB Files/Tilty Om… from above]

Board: 2 copper layers, 38.1 x 50.8 mm, 14 parts (0 on the bottom side), 45 nets.

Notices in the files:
parts and their libraries:
SparkFun-PowerIC: Licensing: CC v3.0 Share-Alike You are welcome to use this library for commercial purposes.
